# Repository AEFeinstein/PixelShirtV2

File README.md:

View this project on [CADLAB.io](https://cadlab.io/project/1073). 

# PixelShirtV2
PixelShirtV2 is an Arduino based collection of video games running on a matrix of WS2812b LEDs and controlled by [ATmega328p based wireless controllers](https://github.com/AEFeinstein/WirelessController). It's meant to be mounted on a shirt, but can be put anywhere.

## The Firmware

The firmware can be compiled two different ways. If one uses the makefile, it compiles as a Linux terminal application that uses the keyboard as input and draws to the terminal using ncurses. This is used for debugging. If one loads it into the Arduino IDE, it compiles as an Arduino executable that uses NRF24L01+ controllers as input and draws to a matrix of WS2812B LEDs.

Each game is a subclass of ArduinoGame. This allows the main function to keep an array of ArduinoGame pointers, and swap between them at runtime. The virtual functions each game must implement are:
* `void UpdatePhysics(void)` - This is called on an IRQ_HZ clock, currently 32Hz. Game state should be updated here.
* `void ProcessInput(int32_t p1, int32_t p2)` - This is called every time there is new player input, which may be more or less often than 32Hz. Each 32 bit parameter contains bitpacked analog joystick and digital button state.
* `void ResetGame(uint8_t isInit, uint8_t whoWon)` - This is called during initialization (noted by isInit). It should reset the game to a known state. It is usually called at the end of each round of a game with which player won (noted by whoWon), though that is game-specific.

The firmware uses the [Adafruit Neopixel Library](https://github.com/adafruit/Adafruit_NeoPixel) to drive the WS2812B LEDs.

The firmware uses the [nrf24L01+ Radio Library](https://github.com/kehribar/nrf24L01_plus) to talk to the controllers.

The current game roster is
* Pong - Move your paddle and don't let the ball get past you.
* Team Tetris - Like regular Tetris, but one player slides the piece while the other rotates. Each time a new piece spawns, the player roles swap.
* Lightcycle - Drive around, leaving a trail, and don't crash into either your or your opponent's trail. The field wraps around top-bottom and left-right.
* PixelFighter - A simple 2D fighter. Attack or block high or low and knock off your opponent's life bar,
* Space Invader - Two players shoot upwards as invaders slide to the left, drop, and reverse direction. The more invaders shot, the faster they go.

## The Hardware

The hardware consists of two parts, detailed below. 

### The Console

The first part is the pocket-sized console, which has the Arduino Micro, NRF24L01+ radio, two RJ45 jacks which break out Arduino pins, and two USB connectors which draw power from an external battery. There are two USB connectors because I used an external battery with two USB connectors which could each source 1A. Not that I ever turned the display on to max brightness, but 2A never hurt anyone...

Screenshots of the PCB layout, the top view is on the left and the bottom view is on the right:

This is what it looks like all soldered together:
<br>

### The Display

The second part is the chest-sized display, which has 256 WS2812B LEDs and an RJ45 connector to connect to the console for power and data. This is a one layer board, though it uses four 0-ohm resistors to jump over traces.

Screenshot of the PCB layout:
<br>

This is what it looks like all soldered together. Not pictured, RJ45 connector at the end of the cable:
<br>

## The Final Product
Here's me at Magfest 14 wearing the display mounted underneath a shirt and holding two controllers. The PixelShirtV2 is playing the PixelFighter game.
<br>

# Earlier Versions

## Version 1
The first version of the PixelShirt used blue LEDs poked through a t-shirt. The cathodes were soldered together in rows, a layer of insulating fabric was layered, then the anodes were soldered in columns. The 32 rows and columns were controlled by four daisy chained 8-bit shift registers and the display would refresh one row at a time, kind of like a CRT TV.
<br>

The upside to this design was that the LED grid was flexible and comfortable. The downside was that it wasn't mechanically strong (a few solder joints broke), the grid wasn't very regular (I'm not great with fabrics), and it just generally didn't look good. The controllers are [SparkFun Joystick Shield Kits](https://www.sparkfun.com/products/9760). 
<br>

But people seemed to get a kick out of it, so I iterated on the design. I wore it first at Magfest 12, but I think this picture is from AwesomeCon. At the time it only had Pong, Lightcycle, and Tetris.
<br>

## Version 2.0
The next year I swapped out the display for the giant PCB with RGB LEDs. Pros: colors! mechanical strength! no undershirt required! Cons: less flexible. I kept the same Sparkfun controllers. I wore this one at Magfest 13. With the advent of color, I added Space Invader.
<br>

## Version 2.1
For Magfest 14, I got over my fear of non-tethered controllers and made [wireless ones](https://github.com/AEFeinstein/WirelessController), which are mentioned above. They worked great and I didn't lose either one, but I did accidentally short their batteries a little when carelessly throwing them in a pocket. They got warm, but no harm no foul.

## Version 2.2
Magfest 15 only had software updates. I added the Fighter and Super Square games. There were no changes for Magfest 16, and I ended up not wearing it at all :(

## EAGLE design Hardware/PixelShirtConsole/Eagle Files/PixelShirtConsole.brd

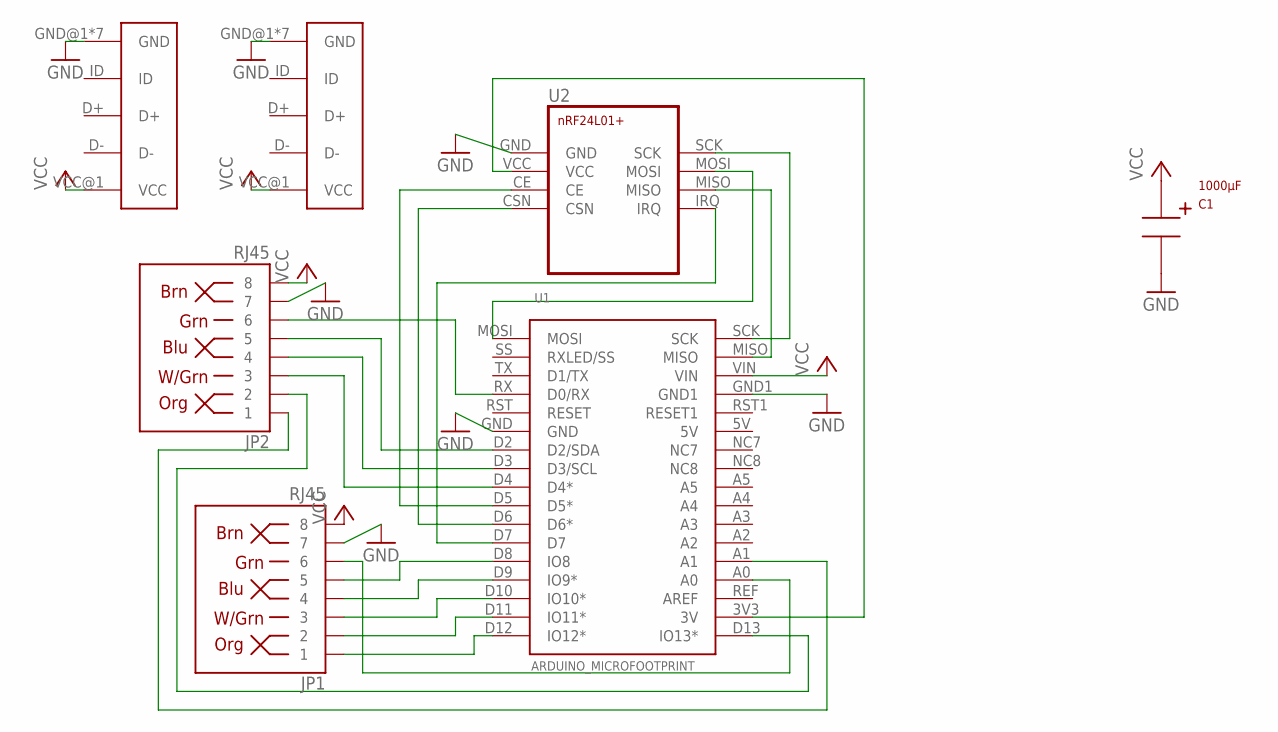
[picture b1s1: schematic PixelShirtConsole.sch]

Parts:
C1: 1000µF; CAP-CUSTOM
JP1, JP2: RJ45; RJ45-8
JP3, JP4: USB-MICRO-B
U1: ARDUINO_MICROFOOTPRINT; ARDUINO-MICRO
U2: NRF24L01+

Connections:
GND: C1.GND, JP1.7, JP2.7, JP3.GND@1 (GND), JP3.GND@2 (GND), JP3.GND@3 (GND), JP3.GND@5 (GND), JP3.GND@6 (GND), JP3.GND@7 (GND), JP3.GNF@4 (GND), JP4.GND@1 (GND), JP4.GND@2 (GND), JP4.GND@3 (GND), JP4.GND@5 (GND), JP4.GND@6 (GND), JP4.GND@7 (GND), JP4.GNF@4 (GND), U1.GND, U1.GND1, U2.GND
unnamed: U1.MISO, U2.MISO
unnamed: U1.SCK, U2.SCK
unnamed: U1.D6 (D6*), U2.CSN
unnamed: U1.D5 (D5*), U2.CE
unnamed: U1.MOSI, U2.MOSI
unnamed: U1.D7, U2.IRQ
unnamed: JP1.2, U1.D11 (IO11*)
unnamed: JP1.3, U1.D10 (IO10*)
unnamed: JP1.4, U1.D9 (IO9*)
unnamed: JP1.1, U1.D12 (IO12*)
unnamed: JP1.6, U1.A0
unnamed: JP1.5, U1.D8 (IO8)
unnamed: JP2.5, U1.D2 (D2/SDA)
unnamed: JP2.4, U1.D3 (D3/SCL)
unnamed: JP2.3, U1.D4 (D4*)
unnamed: JP2.6, U1.RX (D0/RX)
unnamed: JP2.1, U1.A1
unnamed: JP2.2, U1.D13 (IO13*)
unnamed: U1.3V3 (3V), U2.VCC
VCC: C1.VCC, JP1.8, JP2.8, JP3.VCC@1 (VCC), JP4.VCC@1 (VCC), U1.VIN

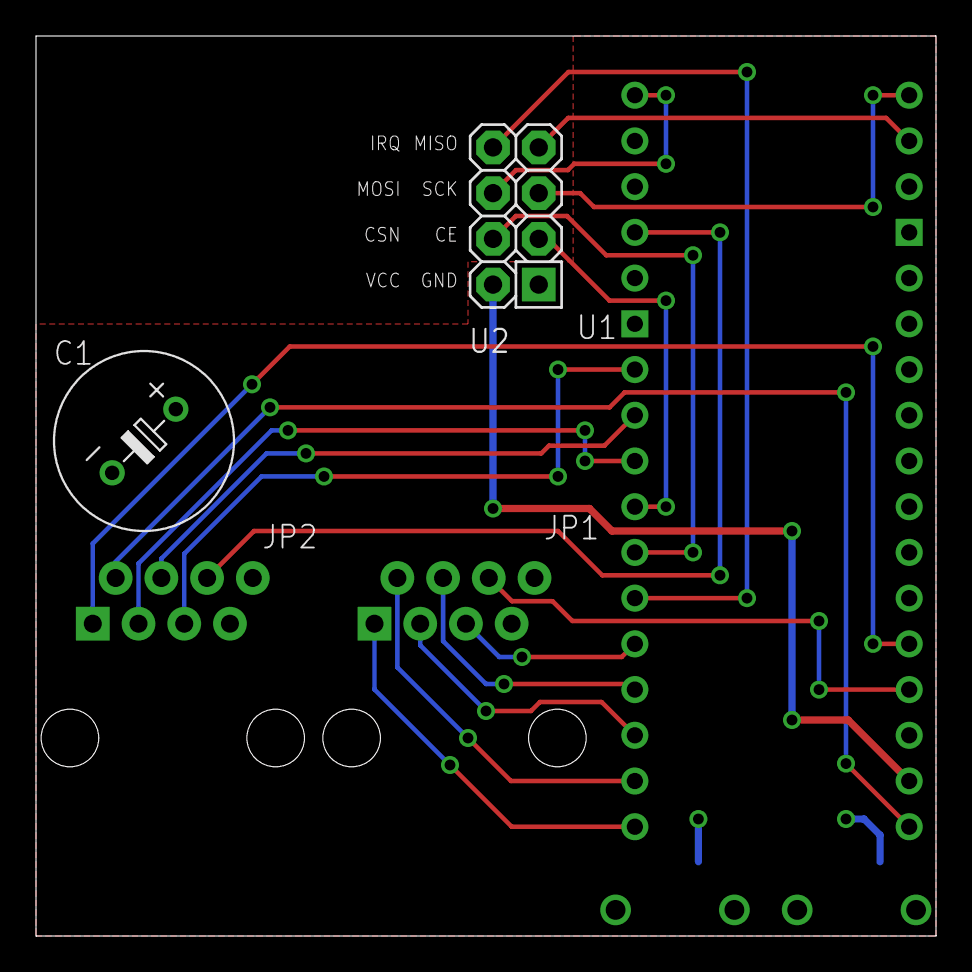
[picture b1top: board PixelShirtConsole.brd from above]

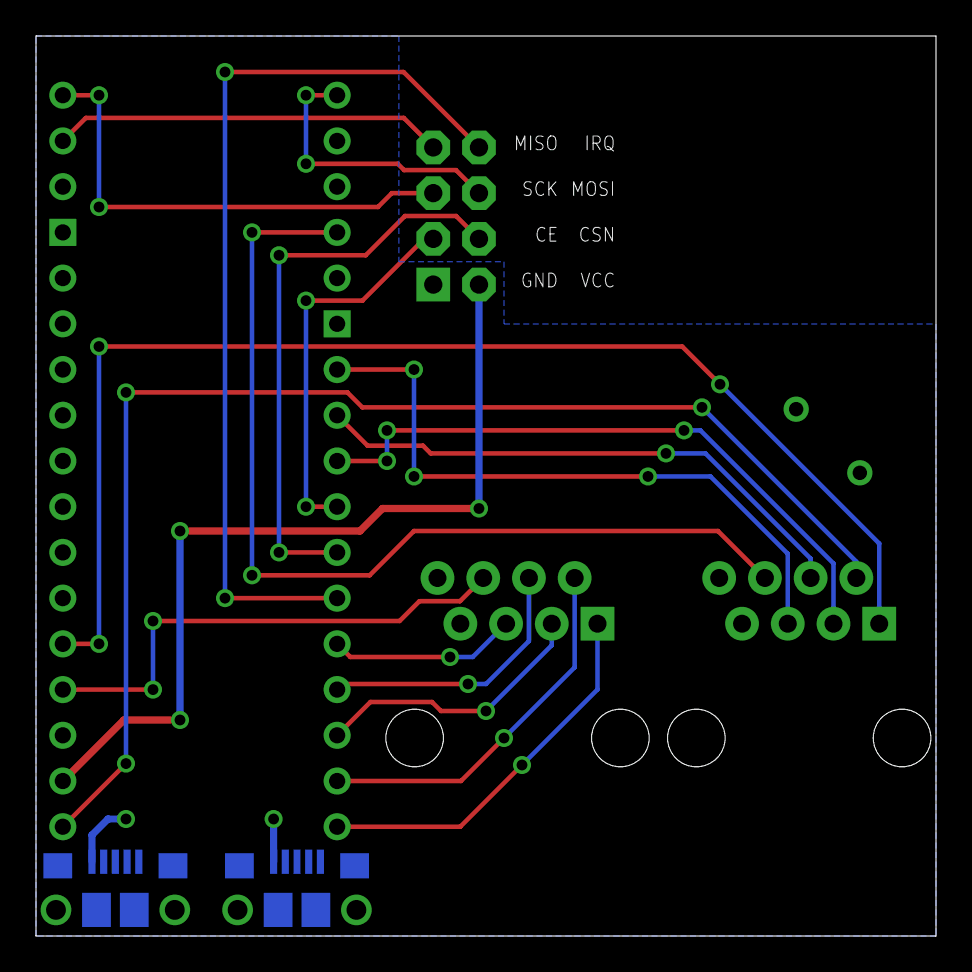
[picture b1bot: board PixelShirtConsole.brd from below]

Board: 2 copper layers, 50.0 x 50.0 mm, 7 parts (2 on the bottom side), 21 nets.

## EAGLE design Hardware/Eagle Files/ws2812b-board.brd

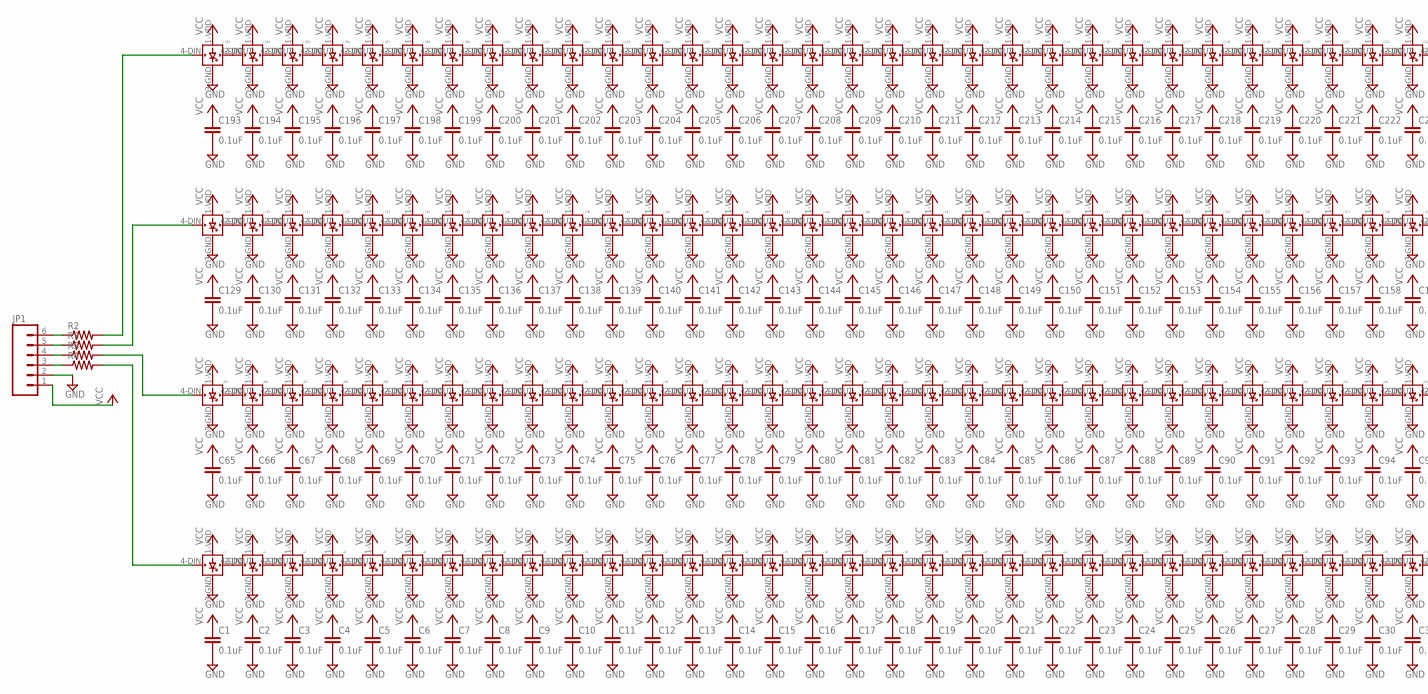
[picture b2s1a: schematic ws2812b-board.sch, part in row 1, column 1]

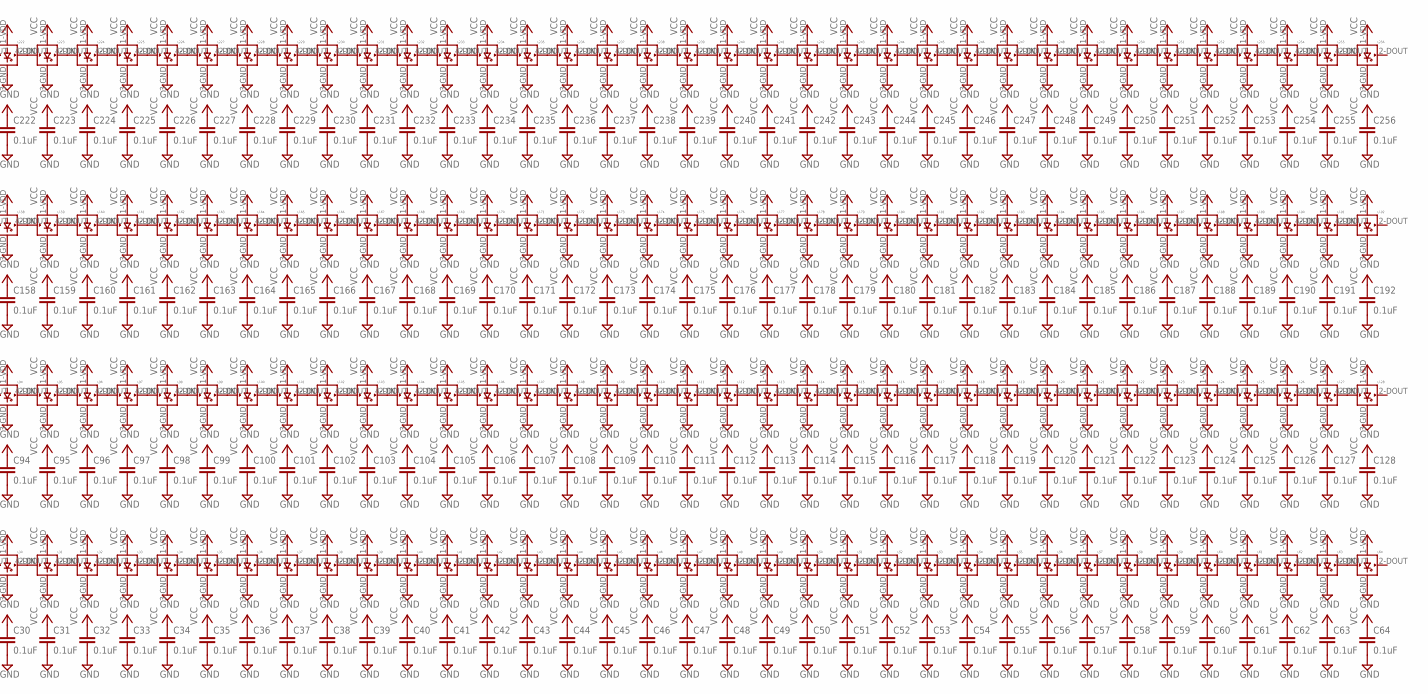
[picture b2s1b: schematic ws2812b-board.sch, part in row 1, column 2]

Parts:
C1, C2, C3, C4, C5, C6, C7, C8, C9, C10, C11, C12, C13, C14, C15, C16, C17, C18, C19, C20, C21, C22, C23, C24, C25, C26, C27, C28, C29, C30, C31, C32, C33, C34, C35, C36, C37, C38, C39, C40, C41, C42, C43, C44, C45, C46, C47, C48, C49, C50, C51, C52, C53, C54, C55, C56, C57, C58, C59, C60, C61, C62, C63, C64, C65, C66, C67, C68, C69, C70, C71, C72, C73, C74, C75, C76, C77, C78, C79, C80, C81, C82, C83, C84, C85, C86, C87, C88, C89, C90, C91, C92, C93, C94, C95, C96, C97, C98, C99, C100, C101, C102, C103, C104, C105, C106, C107, C108, C109, C110, C111, C112, C113, C114, C115, C116, C117, C118, C119, C120, C121, C122, C123, C124, C125, C126, C127, C128, C129, C130, C131, C132, C133, C134, C135, C136, C137, C138, C139, C140, C141, C142, C143, C144, C145, C146, C147, C148, C149, C150, C151, C152, C153, C154, C155, C156, C157, C158, C159, C160, C161, C162, C163, C164, C165, C166, C167, C168, C169, C170, C171, C172, C173, C174, C175, C176, C177, C178, C179, C180, C181, C182, C183, C184, C185, C186, C187, C188, C189, C190, C191, C192, C193, C194, C195, C196, C197, C198, C199, C200, C201, C202, C203, C204, C205, C206, C207, C208, C209, C210, C211, C212, C213, C214, C215, C216, C217, C218, C219, C220, C221, C222, C223, C224, C225, C226, C227, C228, C229, C230, C231, C232, C233, C234, C235, C236, C237, C238, C239, C240, C241, C242, C243, C244, C245, C246, C247, C248, C249, C250, C251, C252, C253, C254, C255, C256: 0.1uF; 0603-CAP
JP1: M06SIP; 1X06
L1, L2, L3, L4, L5, L6, L7, L8, L9, L10, L11, L12, L13, L14, L15, L16, L17, L18, L19, L20, L21, L22, L23, L24, L25, L26, L27, L28, L29, L30, L31, L32, L33, L34, L35, L36, L37, L38, L39, L40, L41, L42, L43, L44, L45, L46, L47, L48, L49, L50, L51, L52, L53, L54, L55, L56, L57, L58, L59, L60, L61, L62, L63, L64, L65, L66, L67, L68, L69, L70, L71, L72, L73, L74, L75, L76, L77, L78, L79, L80, L81, L82, L83, L84, L85, L86, L87, L88, L89, L90, L91, L92, L93, L94, L95, L96, L97, L98, L99, L100, L101, L102, L103, L104, L105, L106, L107, L108, L109, L110, L111, L112, L113, L114, L115, L116, L117, L118, L119, L120, L121, L122, L123, L124, L125, L126, L127, L128, L129, L130, L131, L132, L133, L134, L135, L136, L137, L138, L139, L140, L141, L142, L143, L144, L145, L146, L147, L148, L149, L150, L151, L152, L153, L154, L155, L156, L157, L158, L159, L160, L161, L162, L163, L164, L165, L166, L167, L168, L169, L170, L171, L172, L173, L174, L175, L176, L177, L178, L179, L180, L181, L182, L183, L184, L185, L186, L187, L188, L189, L190, L191, L192, L193, L194, L195, L196, L197, L198, L199, L200, L201, L202, L203, L204, L205, L206, L207, L208, L209, L210, L211, L212, L213, L214, L215, L216, L217, L218, L219, L220, L221, L222, L223, L224, L225, L226, L227, L228, L229, L230, L231, L232, L233, L234, L235, L236, L237, L238, L239, L240, L241, L242, L243, L244, L245, L246, L247, L248, L249, L250, L251, L252, L253, L254, L255, L256: WS2812B
R2, R3, R4, R5: RESISTOR0805-RES; 0805

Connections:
GND: C1.2, C2.2, C3.2, C4.2, C5.2, C6.2, C7.2, C8.2, C9.2, C10.2, C11.2, C12.2, C13.2, C14.2, C15.2, C16.2, C17.2, C18.2, C19.2, C20.2, C21.2, C22.2, C23.2, C24.2, C25.2, C26.2, C27.2, C28.2, C29.2, C30.2, C31.2, C32.2, C33.2, C34.2, C35.2, C36.2, C37.2, C38.2, C39.2, C40.2, C41.2, C42.2, C43.2, C44.2, C45.2, C46.2, C47.2, C48.2, C49.2, C50.2, C51.2, C52.2, C53.2, C54.2, C55.2, C56.2, C57.2, C58.2, C59.2, C60.2, C61.2, C62.2, C63.2, C64.2, C65.2, C66.2, C67.2, C68.2, C69.2, C70.2, C71.2, C72.2, C73.2, C74.2, C75.2, C76.2, C77.2, C78.2, C79.2, C80.2, C81.2, C82.2, C83.2, C84.2, C85.2, C86.2, C87.2, C88.2, C89.2, C90.2, C91.2, C92.2, C93.2, C94.2, C95.2, C96.2, C97.2, C98.2, C99.2, C100.2, C101.2, C102.2, C103.2, C104.2, C105.2, C106.2, C107.2, C108.2, C109.2, C110.2, C111.2, C112.2, C113.2, C114.2, C115.2, C116.2, C117.2, C118.2, C119.2, C120.2, C121.2, C122.2, C123.2, C124.2, C125.2, C126.2, C127.2, C128.2, C129.2, C130.2, C131.2, C132.2, C133.2, C134.2, C135.2, C136.2, C137.2, C138.2, C139.2, C140.2, C141.2, C142.2, C143.2, C144.2, C145.2, C146.2, C147.2, C148.2, C149.2, C150.2, C151.2, C152.2, C153.2, C154.2, C155.2, C156.2, C157.2, C158.2, C159.2, C160.2, C161.2, C162.2, C163.2, C164.2, C165.2, C166.2, C167.2, C168.2, C169.2, C170.2, C171.2, C172.2, C173.2, C174.2, C175.2, C176.2, C177.2, C178.2, C179.2, C180.2, C181.2, C182.2, C183.2, C184.2, C185.2, C186.2, C187.2, C188.2, C189.2, C190.2, C191.2, C192.2, C193.2, C194.2, C195.2, C196.2, C197.2, C198.2, C199.2, C200.2, C201.2, C202.2, C203.2, C204.2, C205.2, C206.2, C207.2, C208.2, C209.2, C210.2, C211.2, C212.2, C213.2, C214.2, C215.2, C216.2, C217.2, C218.2, C219.2, C220.2, C221.2, C222.2, C223.2, C224.2, C225.2, C226.2, C227.2, C228.2, C229.2, C230.2, C231.2, C232.2, C233.2, C234.2, C235.2, C236.2, C237.2, C238.2, C239.2, C240.2, C241.2, C242.2, C243.2, C244.2, C245.2, C246.2, C247.2, C248.2, C249.2, C250.2, C251.2, C252.2, C253.2, C254.2, C255.2, C256.2, JP1.2, L1.3-GND (GND), L2.3-GND (GND), L3.3-GND (GND), L4.3-GND (GND), L5.3-GND (GND), L6.3-GND (GND), L7.3-GND (GND), L8.3-GND (GND), L9.3-GND (GND), L10.3-GND (GND), L11.3-GND (GND), L12.3-GND (GND), L13.3-GND (GND), L14.3-GND (GND), L15.3-GND (GND), L16.3-GND (GND), L17.3-GND (GND), L18.3-GND (GND), L19.3-GND (GND), L20.3-GND (GND), L21.3-GND (GND), L22.3-GND (GND), L23.3-GND (GND), L24.3-GND (GND), L25.3-GND (GND), L26.3-GND (GND), L27.3-GND (GND), L28.3-GND (GND), L29.3-GND (GND), L30.3-GND (GND), L31.3-GND (GND), L32.3-GND (GND), L33.3-GND (GND), L34.3-GND (GND), L35.3-GND (GND), L36.3-GND (GND), L37.3-GND (GND), L38.3-GND (GND), L39.3-GND (GND), L40.3-GND (GND), L41.3-GND (GND), L42.3-GND (GND), L43.3-GND (GND), L44.3-GND (GND), L45.3-GND (GND), L46.3-GND (GND), L47.3-GND (GND), L48.3-GND (GND), L49.3-GND (GND), L50.3-GND (GND), L51.3-GND (GND), L52.3-GND (GND), L53.3-GND (GND), L54.3-GND (GND), L55.3-GND (GND), L56.3-GND (GND), L57.3-GND (GND), L58.3-GND (GND), L59.3-GND (GND), L60.3-GND (GND), L61.3-GND (GND), L62.3-GND (GND), L63.3-GND (GND), L64.3-GND (GND), L65.3-GND (GND), L66.3-GND (GND), L67.3-GND (GND), L68.3-GND (GND), L69.3-GND (GND), L70.3-GND (GND), L71.3-GND (GND), L72.3-GND (GND), L73.3-GND (GND), L74.3-GND (GND), L75.3-GND (GND), L76.3-GND (GND), L77.3-GND (GND), L78.3-GND (GND), L79.3-GND (GND), L80.3-GND (GND), L81.3-GND (GND), L82.3-GND (GND), L83.3-GND (GND), L84.3-GND (GND), L85.3-GND (GND), L86.3-GND (GND), L87.3-GND (GND), L88.3-GND (GND), L89.3-GND (GND), L90.3-GND (GND), L91.3-GND (GND), L92.3-GND (GND), L93.3-GND (GND), L94.3-GND (GND), L95.3-GND (GND), L96.3-GND (GND), L97.3-GND (GND), L98.3-GND (GND), L99.3-GND (GND), L100.3-GND (GND), L101.3-GND (GND), L102.3-GND (GND), L103.3-GND (GND), L104.3-GND (GND), L105.3-GND (GND), L106.3-GND (GND), L107.3-GND (GND), L108.3-GND (GND), L109.3-GND (GND), L110.3-GND (GND), L111.3-GND (GND), L112.3-GND (GND), L113.3-GND (GND), L114.3-GND (GND), L115.3-GND (GND), L116.3-GND (GND), L117.3-GND (GND), L118.3-GND (GND), L119.3-GND (GND), L120.3-GND (GND), L121.3-GND (GND), L122.3-GND (GND), L123.3-GND (GND), L124.3-GND (GND), L125.3-GND (GND), L126.3-GND (GND), L127.3-GND (GND), L128.3-GND (GND), L129.3-GND (GND), L130.3-GND (GND), L131.3-GND (GND), L132.3-GND (GND), L133.3-GND (GND), L134.3-GND (GND), L135.3-GND (GND), L136.3-GND (GND), L137.3-GND (GND), L138.3-GND (GND), L139.3-GND (GND), L140.3-GND (GND), L141.3-GND (GND), L142.3-GND (GND), L143.3-GND (GND), L144.3-GND (GND), L145.3-GND (GND), L146.3-GND (GND), L147.3-GND (GND), L148.3-GND (GND), L149.3-GND (GND), L150.3-GND (GND), L151.3-GND (GND), L152.3-GND (GND), L153.3-GND (GND)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
unnamed: L1.2-DOUT (DOUT), L2.4-DIN (DIN)
unnamed: L2.2-DOUT (DOUT), L3.4-DIN (DIN)
unnamed: L3.2-DOUT (DOUT), L4.4-DIN (DIN)
unnamed: L4.2-DOUT (DOUT), L5.4-DIN (DIN)
unnamed: L5.2-DOUT (DOUT), L6.4-DIN (DIN)
unnamed: L6.2-DOUT (DOUT), L7.4-DIN (DIN)
unnamed: L7.2-DOUT (DOUT), L8.4-DIN (DIN)
unnamed: L8.2-DOUT (DOUT), L9.4-DIN (DIN)
unnamed: L9.2-DOUT (DOUT), L10.4-DIN (DIN)
unnamed: L10.2-DOUT (DOUT), L11.4-DIN (DIN)
unnamed: L11.2-DOUT (DOUT), L12.4-DIN (DIN)
unnamed: L12.2-DOUT (DOUT), L13.4-DIN (DIN)
unnamed: L13.2-DOUT (DOUT), L14.4-DIN (DIN)
unnamed: L14.2-DOUT (DOUT), L15.4-DIN (DIN)
unnamed: L15.2-DOUT (DOUT), L16.4-DIN (DIN)
unnamed: L16.2-DOUT (DOUT), L17.4-DIN (DIN)
unnamed: L17.2-DOUT (DOUT), L18.4-DIN (DIN)
unnamed: L18.2-DOUT (DOUT), L19.4-DIN (DIN)
unnamed: L19.2-DOUT (DOUT), L20.4-DIN (DIN)
unnamed: L20.2-DOUT (DOUT), L21.4-DIN (DIN)
unnamed: L21.2-DOUT (DOUT), L22.4-DIN (DIN)
unnamed: L22.2-DOUT (DOUT), L23.4-DIN (DIN)
unnamed: L23.2-DOUT (DOUT), L24.4-DIN (DIN)
unnamed: L24.2-DOUT (DOUT), L25.4-DIN (DIN)
unnamed: L25.2-DOUT (DOUT), L26.4-DIN (DIN)
unnamed: L26.2-DOUT (DOUT), L27.4-DIN (DIN)
unnamed: L27.2-DOUT (DOUT), L28.4-DIN (DIN)
unnamed: L28.2-DOUT (DOUT), L29.4-DIN (DIN)
unnamed: L29.2-DOUT (DOUT), L30.4-DIN (DIN)
unnamed: L30.2-DOUT (DOUT), L31.4-DIN (DIN)
unnamed: L31.2-DOUT (DOUT), L32.4-DIN (DIN)
unnamed: L32.2-DOUT (DOUT), L33.4-DIN (DIN)
unnamed: L33.2-DOUT (DOUT), L34.4-DIN (DIN)
unnamed: L34.2-DOUT (DOUT), L35.4-DIN (DIN)
unnamed: L35.2-DOUT (DOUT), L36.4-DIN (DIN)
unnamed: L36.2-DOUT (DOUT), L37.4-DIN (DIN)
unnamed: L37.2-DOUT (DOUT), L38.4-DIN (DIN)
unnamed: L38.2-DOUT (DOUT), L39.4-DIN (DIN)
unnamed: L39.2-DOUT (DOUT), L40.4-DIN (DIN)
unnamed: L40.2-DOUT (DOUT), L41.4-DIN (DIN)
unnamed: L41.2-DOUT (DOUT), L42.4-DIN (DIN)
unnamed: L42.2-DOUT (DOUT), L43.4-DIN (DIN)
unnamed: L43.2-DOUT (DOUT), L44.4-DIN (DIN)
unnamed: L44.2-DOUT (DOUT), L45.4-DIN (DIN)
unnamed: L45.2-DOUT (DOUT), L46.4-DIN (DIN)
unnamed: L46.2-DOUT (DOUT), L47.4-DIN (DIN)
unnamed: L47.2-DOUT (DOUT), L48.4-DIN (DIN)
unnamed: L48.2-DOUT (DOUT), L49.4-DIN (DIN)
unnamed: L49.2-DOUT (DOUT), L50.4-DIN (DIN)
unnamed: L50.2-DOUT (DOUT), L51.4-DIN (DIN)
unnamed: L51.2-DOUT (DOUT), L52.4-DIN (DIN)
unnamed: L52.2-DOUT (DOUT), L53.4-DIN (DIN)
unnamed: L53.2-DOUT (DOUT), L54.4-DIN (DIN)
unnamed: L54.2-DOUT (DOUT), L55.4-DIN (DIN)
unnamed: L55.2-DOUT (DOUT), L56.4-DIN (DIN)
unnamed: L56.2-DOUT (DOUT), L57.4-DIN (DIN)
unnamed: L57.2-DOUT (DOUT), L58.4-DIN (DIN)
unnamed: L58.2-DOUT (DOUT), L59.4-DIN (DIN)
unnamed: L59.2-DOUT (DOUT), L60.4-DIN (DIN)
unnamed: L60.2-DOUT (DOUT), L61.4-DIN (DIN)
unnamed: L61.2-DOUT (DOUT), L62.4-DIN (DIN)
unnamed: L62.2-DOUT (DOUT), L63.4-DIN (DIN)
unnamed: L63.2-DOUT (DOUT), L64.4-DIN (DIN)
unnamed: L65.2-DOUT (DOUT), L66.4-DIN (DIN)
unnamed: L66.2-DOUT (DOUT), L67.4-DIN (DIN)
unnamed: L67.2-DOUT (DOUT), L68.4-DIN (DIN)
unnamed: L68.2-DOUT (DOUT), L69.4-DIN (DIN)
unnamed: L69.2-DOUT (DOUT), L70.4-DIN (DIN)
unnamed: L70.2-DOUT (DOUT), L71.4-DIN (DIN)
unnamed: L71.2-DOUT (DOUT), L72.4-DIN (DIN)
unnamed: L72.2-DOUT (DOUT), L73.4-DIN (DIN)
unnamed: L73.2-DOUT (DOUT), L74.4-DIN (DIN)
unnamed: L74.2-DOUT (DOUT), L75.4-DIN (DIN)
unnamed: L75.2-DOUT (DOUT), L76.4-DIN (DIN)
unnamed: L76.2-DOUT (DOUT), L77.4-DIN (DIN)
unnamed: L77.2-DOUT (DOUT), L78.4-DIN (DIN)
unnamed: L78.2-DOUT (DOUT), L79.4-DIN (DIN)
unnamed: L79.2-DOUT (DOUT), L80.4-DIN (DIN)
unnamed: L80.2-DOUT (DOUT), L81.4-DIN (DIN)
unnamed: L81.2-DOUT (DOUT), L82.4-DIN (DIN)
unnamed: L82.2-DOUT (DOUT), L83.4-DIN (DIN)
unnamed: L83.2-DOUT (DOUT), L84.4-DIN (DIN)
unnamed: L84.2-DOUT (DOUT), L85.4-DIN (DIN)
unnamed: L85.2-DOUT (DOUT), L86.4-DIN (DIN)
unnamed: L86.2-DOUT (DOUT), L87.4-DIN (DIN)
unnamed: L87.2-DOUT (DOUT), L88.4-DIN (DIN)
unnamed: L88.2-DOUT (DOUT), L89.4-DIN (DIN)
unnamed: L89.2-DOUT (DOUT), L90.4-DIN (DIN)
unnamed: L90.2-DOUT (DOUT), L91.4-DIN (DIN)
unnamed: L91.2-DOUT (DOUT), L92.4-DIN (DIN)
unnamed: L92.2-DOUT (DOUT), L93.4-DIN (DIN)
unnamed: L93.2-DOUT (DOUT), L94.4-DIN (DIN)
unnamed: L94.2-DOUT (DOUT), L95.4-DIN (DIN)
unnamed: L95.2-DOUT (DOUT), L96.4-DIN (DIN)
unnamed: L96.2-DOUT (DOUT), L97.4-DIN (DIN)
unnamed: L97.2-DOUT (DOUT), L98.4-DIN (DIN)
unnamed: L98.2-DOUT (DOUT), L99.4-DIN (DIN)
unnamed: L99.2-DOUT (DOUT), L100.4-DIN (DIN)
unnamed: L100.2-DOUT (DOUT), L101.4-DIN (DIN)
unnamed: L101.2-DOUT (DOUT), L102.4-DIN (DIN)
unnamed: L102.2-DOUT (DOUT), L103.4-DIN (DIN)
unnamed: L103.2-DOUT (DOUT), L104.4-DIN (DIN)
unnamed: L104.2-DOUT (DOUT), L105.4-DIN (DIN)
unnamed: L105.2-DOUT (DOUT), L106.4-DIN (DIN)
unnamed: L106.2-DOUT (DOUT), L107.4-DIN (DIN)
unnamed: L107.2-DOUT (DOUT), L108.4-DIN (DIN)
unnamed: L108.2-DOUT (DOUT), L109.4-DIN (DIN)
unnamed: L109.2-DOUT (DOUT), L110.4-DIN (DIN)
unnamed: L110.2-DOUT (DOUT), L111.4-DIN (DIN)
unnamed: L111.2-DOUT (DOUT), L112.4-DIN (DIN)
unnamed: L112.2-DOUT (DOUT), L113.4-DIN (DIN)
unnamed: L113.2-DOUT (DOUT), L114.4-DIN (DIN)
unnamed: L114.2-DOUT (DOUT), L115.4-DIN (DIN)
unnamed: L115.2-DOUT (DOUT), L116.4-DIN (DIN)
unnamed: L116.2-DOUT (DOUT), L117.4-DIN (DIN)
unnamed: L117.2-DOUT (DOUT), L118.4-DIN (DIN)
unnamed: L118.2-DOUT (DOUT), L119.4-DIN (DIN)
unnamed: L119.2-DOUT (DOUT), L120.4-DIN (DIN)
unnamed: L120.2-DOUT (DOUT), L121.4-DIN (DIN)
unnamed: L121.2-DOUT (DOUT), L122.4-DIN (DIN)
unnamed: L122.2-DOUT (DOUT), L123.4-DIN (DIN)
unnamed: L123.2-DOUT (DOUT), L124.4-DIN (DIN)
unnamed: L124.2-DOUT (DOUT), L125.4-DIN (DIN)
unnamed: L125.2-DOUT (DOUT), L126.4-DIN (DIN)
unnamed: L126.2-DOUT (DOUT), L127.4-DIN (DIN)
unnamed: L127.2-DOUT (DOUT), L128.4-DIN (DIN)
unnamed: L129.2-DOUT (DOUT), L130.4-DIN (DIN)
unnamed: L130.2-DOUT (DOUT), L131.4-DIN (DIN)
unnamed: L131.2-DOUT (DOUT), L132.4-DIN (DIN)
unnamed: L132.2-DOUT (DOUT), L133.4-DIN (DIN)
unnamed: L133.2-DOUT (DOUT), L134.4-DIN (DIN)
unnamed: L134.2-DOUT (DOUT), L135.4-DIN (DIN)
unnamed: L135.2-DOUT (DOUT), L136.4-DIN (DIN)
unnamed: L136.2-DOUT (DOUT), L137.4-DIN (DIN)
unnamed: L137.2-DOUT (DOUT), L138.4-DIN (DIN)
unnamed: L138.2-DOUT (DOUT), L139.4-DIN (DIN)
unnamed: L139.2-DOUT (DOUT), L140.4-DIN (DIN)
unnamed: L140.2-DOUT (DOUT), L141.4-DIN (DIN)
unnamed: L141.2-DOUT (DOUT), L142.4-DIN (DIN)
unnamed: L142.2-DOUT (DOUT), L143.4-DIN (DIN)
unnamed: L143.2-DOUT (DOUT), L144.4-DIN (DIN)
unnamed: L144.2-DOUT (DOUT), L145.4-DIN (DIN)
unnamed: L145.2-DOUT (DOUT), L146.4-DIN (DIN)
unnamed: L146.2-DOUT (DOUT), L147.4-DIN (DIN)
unnamed: L147.2-DOUT (DOUT), L148.4-DIN (DIN)
unnamed: L148.2-DOUT (DOUT), L149.4-DIN (DIN)
unnamed: L149.2-DOUT (DOUT), L150.4-DIN (DIN)
unnamed: L150.2-DOUT (DOUT), L151.4-DIN (DIN)
unnamed: L151.2-DOUT (DOUT), L152.4-DIN (DIN)
unnamed: L152.2-DOUT (DOUT), L153.4-DIN (DIN)
unnamed: L153.2-DOUT (DOUT), L154.4-DIN (DIN)
unnamed: L154.2-DOUT (DOUT), L155.4-DIN (DIN)
unnamed: L155.2-DOUT (DOUT), L156.4-DIN (DIN)
unnamed: L156.2-DOUT (DOUT), L157.4-DIN (DIN)
unnamed: L157.2-DOUT (DOUT), L158.4-DIN (DIN)
unnamed: L158.2-DOUT (DOUT), L159.4-DIN (DIN)
unnamed: L159.2-DOUT (DOUT), L160.4-DIN (DIN)
unnamed: L160.2-DOUT (DOUT), L161.4-DIN (DIN)
unnamed: L161.2-DOUT (DOUT), L162.4-DIN (DIN)
unnamed: L162.2-DOUT (DOUT), L163.4-DIN (DIN)
unnamed: L163.2-DOUT (DOUT), L164.4-DIN (DIN)
unnamed: L164.2-DOUT (DOUT), L165.4-DIN (DIN)
unnamed: L165.2-DOUT (DOUT), L166.4-DIN (DIN)
unnamed: L166.2-DOUT (DOUT), L167.4-DIN (DIN)
unnamed: L167.2-DOUT (DOUT), L168.4-DIN (DIN)
unnamed: L168.2-DOUT (DOUT), L169.4-DIN (DIN)
unnamed: L169.2-DOUT (DOUT), L170.4-DIN (DIN)
unnamed: L170.2-DOUT (DOUT), L171.4-DIN (DIN)
unnamed: L171.2-DOUT (DOUT), L172.4-DIN (DIN)
unnamed: L172.2-DOUT (DOUT), L173.4-DIN (DIN)
unnamed: L173.2-DOUT (DOUT), L174.4-DIN (DIN)
unnamed: L174.2-DOUT (DOUT), L175.4-DIN (DIN)
unnamed: L175.2-DOUT (DOUT), L176.4-DIN (DIN)
unnamed: L176.2-DOUT (DOUT), L177.4-DIN (DIN)
unnamed: L177.2-DOUT (DOUT), L178.4-DIN (DIN)
unnamed: L178.2-DOUT (DOUT), L179.4-DIN (DIN)
unnamed: L179.2-DOUT (DOUT), L180.4-DIN (DIN)
unnamed: L180.2-DOUT (DOUT), L181.4-DIN (DIN)
unnamed: L181.2-DOUT (DOUT), L182.4-DIN (DIN)
unnamed: L182.2-DOUT (DOUT), L183.4-DIN (DIN)
unnamed: L183.2-DOUT (DOUT), L184.4-DIN (DIN)
unnamed: L184.2-DOUT (DOUT), L185.4-DIN (DIN)
unnamed: L185.2-DOUT (DOUT), L186.4-DIN (DIN)
unnamed: L186.2-DOUT (DOUT), L187.4-DIN (DIN)
unnamed: L187.2-DOUT (DOUT), L188.4-DIN (DIN)
unnamed: L188.2-DOUT (DOUT), L189.4-DIN (DIN)
unnamed: L189.2-DOUT (DOUT), L190.4-DIN (DIN)
unnamed: L190.2-DOUT (DOUT), L191.4-DIN (DIN)
unnamed: L191.2-DOUT (DOUT), L192.4-DIN (DIN)
unnamed: L193.2-DOUT (DOUT), L194.4-DIN (DIN)
unnamed: L194.2-DOUT (DOUT), L195.4-DIN (DIN)
unnamed: L195.2-DOUT (DOUT), L196.4-DIN (DIN)
unnamed: L196.2-DOUT (DOUT), L197.4-DIN (DIN)
unnamed: L197.2-DOUT (DOUT), L198.4-DIN (DIN)
unnamed: L198.2-DOUT (DOUT), L199.4-DIN (DIN)
unnamed: L199.2-DOUT (DOUT), L200.4-DIN (DIN)
unnamed: L200.2-DOUT (DOUT), L201.4-DIN (DIN)
unnamed: L201.2-DOUT (DOUT), L202.4-DIN (DIN)
unnamed: L202.2-DOUT (DOUT), L203.4-DIN (DIN)
unnamed: L203.2-DOUT (DOUT), L204.4-DIN (DIN)
unnamed: L204.2-DOUT (DOUT), L205.4-DIN (DIN)
unnamed: L205.2-DOUT (DOUT), L206.4-DIN (DIN)
unnamed: L206.2-DOUT (DOUT), L207.4-DIN (DIN)
unnamed: L207.2-DOUT (DOUT), L208.4-DIN (DIN)
unnamed: L208.2-DOUT (DOUT), L209.4-DIN (DIN)
unnamed: L209.2-DOUT (DOUT), L210.4-DIN (DIN)
unnamed: L210.2-DOUT (DOUT), L211.4-DIN (DIN)
unnamed: L211.2-DOUT (DOUT), L212.4-DIN (DIN)
unnamed: L212.2-DOUT (DOUT), L213.4-DIN (DIN)
unnamed: L213.2-DOUT (DOUT), L214.4-DIN (DIN)
unnamed: L214.2-DOUT (DOUT), L215.4-DIN (DIN)
unnamed: L215.2-DOUT (DOUT), L216.4-DIN (DIN)
unnamed: L216.2-DOUT (DOUT), L217.4-DIN (DIN)
unnamed: L217.2-DOUT (DOUT), L218.4-DIN (DIN)
unnamed: L218.2-DOUT (DOUT), L219.4-DIN (DIN)
unnamed: L219.2-DOUT (DOUT), L220.4-DIN (DIN)
unnamed: L220.2-DOUT (DOUT), L221.4-DIN (DIN)
unnamed: L221.2-DOUT (DOUT), L222.4-DIN (DIN)
unnamed: L222.2-DOUT (DOUT), L223.4-DIN (DIN)
unnamed: L223.2-DOUT (DOUT), L224.4-DIN (DIN)
unnamed: L224.2-DOUT (DOUT), L225.4-DIN (DIN)
unnamed: L225.2-DOUT (DOUT), L226.4-DIN (DIN)
unnamed: L226.2-DOUT (DOUT), L227.4-DIN (DIN)
unnamed: L227.2-DOUT (DOUT), L228.4-DIN (DIN)
unnamed: L228.2-DOUT (DOUT), L229.4-DIN (DIN)
unnamed: L229.2-DOUT (DOUT), L230.4-DIN (DIN)
unnamed: L230.2-DOUT (DOUT), L231.4-DIN (DIN)
unnamed: L231.2-DOUT (DOUT), L232.4-DIN (DIN)
unnamed: L232.2-DOUT (DOUT), L233.4-DIN (DIN)
unnamed: L233.2-DOUT (DOUT), L234.4-DIN (DIN)
unnamed: L234.2-DOUT (DOUT), L235.4-DIN (DIN)
unnamed: L235.2-DOUT (DOUT), L236.4-DIN (DIN)
unnamed: L236.2-DOUT (DOUT), L237.4-DIN (DIN)
unnamed: L237.2-DOUT (DOUT), L238.4-DIN (DIN)
unnamed: L238.2-DOUT (DOUT), L239.4-DIN (DIN)
unnamed: L239.2-DOUT (DOUT), L240.4-DIN (DIN)
unnamed: L240.2-DOUT (DOUT), L241.4-DIN (DIN)
unnamed: L241.2-DOUT (DOUT), L242.4-DIN (DIN)
unnamed: L242.2-DOUT (DOUT), L243.4-DIN (DIN)
unnamed: L243.2-DOUT (DOUT), L244.4-DIN (DIN)
unnamed: L244.2-DOUT (DOUT), L245.4-DIN (DIN)
unnamed: L245.2-DOUT (DOUT), L246.4-DIN (DIN)
unnamed: L246.2-DOUT (DOUT), L247.4-DIN (DIN)
unnamed: L247.2-DOUT (DOUT), L248.4-DIN (DIN)
unnamed: L248.2-DOUT (DOUT), L249.4-DIN (DIN)
unnamed: L249.2-DOUT (DOUT), L250.4-DIN (DIN)
unnamed: L250.2-DOUT (DOUT), L251.4-DIN (DIN)
unnamed: L251.2-DOUT (DOUT), L252.4-DIN (DIN)
unnamed: L252.2-DOUT (DOUT), L253.4-DIN (DIN)
unnamed: L253.2-DOUT (DOUT), L254.4-DIN (DIN)
unnamed: L254.2-DOUT (DOUT), L255.4-DIN (DIN)
unnamed: L255.2-DOUT (DOUT), L256.4-DIN (DIN)
unnamed: L1.4-DIN (DIN), R4.2
unnamed: L65.4-DIN (DIN), R5.2
unnamed: L193.4-DIN (DIN), R2.2
unnamed: L129.4-DIN (DIN), R3.2
unnamed: JP1.6, R2.1
unnamed: JP1.5, R3.1
unnamed: JP1.4, R5.1
unnamed: JP1.3, R4.1
VCC: C1.1, C2.1, C3.1, C4.1, C5.1, C6.1, C7.1, C8.1, C9.1, C10.1, C11.1, C12.1, C13.1, C14.1, C15.1, C16.1, C17.1, C18.1, C19.1, C20.1, C21.1, C22.1, C23.1, C24.1, C25.1, C26.1, C27.1, C28.1, C29.1, C30.1, C31.1, C32.1, C33.1, C34.1, C35.1, C36.1, C37.1, C38.1, C39.1, C40.1, C41.1, C42.1, C43.1, C44.1, C45.1, C46.1, C47.1, C48.1, C49.1, C50.1, C51.1, C52.1, C53.1, C54.1, C55.1, C56.1, C57.1, C58.1, C59.1, C60.1, C61.1, C62.1, C63.1, C64.1, C65.1, C66.1, C67.1, C68.1, C69.1, C70.1, C71.1, C72.1, C73.1, C74.1, C75.1, C76.1, C77.1, C78.1, C79.1, C80.1, C81.1, C82.1, C83.1, C84.1, C85.1, C86.1, C87.1, C88.1, C89.1, C90.1, C91.1, C92.1, C93.1, C94.1, C95.1, C96.1, C97.1, C98.1, C99.1, C100.1, C101.1, C102.1, C103.1, C104.1, C105.1, C106.1, C107.1, C108.1, C109.1, C110.1, C111.1, C112.1, C113.1, C114.1, C115.1, C116.1, C117.1, C118.1, C119.1, C120.1, C121.1, C122.1, C123.1, C124.1, C125.1, C126.1, C127.1, C128.1, C129.1, C130.1, C131.1, C132.1, C133.1, C134.1, C135.1, C136.1, C137.1, C138.1, C139.1, C140.1, C141.1, C142.1, C143.1, C144.1, C145.1, C146.1, C147.1, C148.1, C149.1, C150.1, C151.1, C152.1, C153.1, C154.1, C155.1, C156.1, C157.1, C158.1, C159.1, C160.1, C161.1, C162.1, C163.1, C164.1, C165.1, C166.1, C167.1, C168.1, C169.1, C170.1, C171.1, C172.1, C173.1, C174.1, C175.1, C176.1, C177.1, C178.1, C179.1, C180.1, C181.1, C182.1, C183.1, C184.1, C185.1, C186.1, C187.1, C188.1, C189.1, C190.1, C191.1, C192.1, C193.1, C194.1, C195.1, C196.1, C197.1, C198.1, C199.1, C200.1, C201.1, C202.1, C203.1, C204.1, C205.1, C206.1, C207.1, C208.1, C209.1, C210.1, C211.1, C212.1, C213.1, C214.1, C215.1, C216.1, C217.1, C218.1, C219.1, C220.1, C221.1, C222.1, C223.1, C224.1, C225.1, C226.1, C227.1, C228.1, C229.1, C230.1, C231.1, C232.1, C233.1, C234.1, C235.1, C236.1, C237.1, C238.1, C239.1, C240.1, C241.1, C242.1, C243.1, C244.1, C245.1, C246.1, C247.1, C248.1, C249.1, C250.1, C251.1, C252.1, C253.1, C254.1, C255.1, C256.1, JP1.1, L1.1-VDD (VDD), L2.1-VDD (VDD), L3.1-VDD (VDD), L4.1-VDD (VDD), L5.1-VDD (VDD), L6.1-VDD (VDD), L7.1-VDD (VDD), L8.1-VDD (VDD), L9.1-VDD (VDD), L10.1-VDD (VDD), L11.1-VDD (VDD), L12.1-VDD (VDD), L13.1-VDD (VDD), L14.1-VDD (VDD), L15.1-VDD (VDD), L16.1-VDD (VDD), L17.1-VDD (VDD), L18.1-VDD (VDD), L19.1-VDD (VDD), L20.1-VDD (VDD), L21.1-VDD (VDD), L22.1-VDD (VDD), L23.1-VDD (VDD), L24.1-VDD (VDD), L25.1-VDD (VDD), L26.1-VDD (VDD), L27.1-VDD (VDD), L28.1-VDD (VDD), L29.1-VDD (VDD), L30.1-VDD (VDD), L31.1-VDD (VDD), L32.1-VDD (VDD), L33.1-VDD (VDD), L34.1-VDD (VDD), L35.1-VDD (VDD), L36.1-VDD (VDD), L37.1-VDD (VDD), L38.1-VDD (VDD), L39.1-VDD (VDD), L40.1-VDD (VDD), L41.1-VDD (VDD), L42.1-VDD (VDD), L43.1-VDD (VDD), L44.1-VDD (VDD), L45.1-VDD (VDD), L46.1-VDD (VDD), L47.1-VDD (VDD), L48.1-VDD (VDD), L49.1-VDD (VDD), L50.1-VDD (VDD), L51.1-VDD (VDD), L52.1-VDD (VDD), L53.1-VDD (VDD), L54.1-VDD (VDD), L55.1-VDD (VDD), L56.1-VDD (VDD), L57.1-VDD (VDD), L58.1-VDD (VDD), L59.1-VDD (VDD), L60.1-VDD (VDD), L61.1-VDD (VDD), L62.1-VDD (VDD), L63.1-VDD (VDD), L64.1-VDD (VDD), L65.1-VDD (VDD), L66.1-VDD (VDD), L67.1-VDD (VDD), L68.1-VDD (VDD), L69.1-VDD (VDD), L70.1-VDD (VDD), L71.1-VDD (VDD), L72.1-VDD (VDD), L73.1-VDD (VDD), L74.1-VDD (VDD), L75.1-VDD (VDD), L76.1-VDD (VDD), L77.1-VDD (VDD), L78.1-VDD (VDD), L79.1-VDD (VDD), L80.1-VDD (VDD), L81.1-VDD (VDD), L82.1-VDD (VDD), L83.1-VDD (VDD), L84.1-VDD (VDD), L85.1-VDD (VDD), L86.1-VDD (VDD), L87.1-VDD (VDD), L88.1-VDD (VDD), L89.1-VDD (VDD), L90.1-VDD (VDD), L91.1-VDD (VDD), L92.1-VDD (VDD), L93.1-VDD (VDD), L94.1-VDD (VDD), L95.1-VDD (VDD), L96.1-VDD (VDD), L97.1-VDD (VDD), L98.1-VDD (VDD), L99.1-VDD (VDD), L100.1-VDD (VDD), L101.1-VDD (VDD), L102.1-VDD (VDD), L103.1-VDD (VDD), L104.1-VDD (VDD), L105.1-VDD (VDD), L106.1-VDD (VDD), L107.1-VDD (VDD), L108.1-VDD (VDD), L109.1-VDD (VDD), L110.1-VDD (VDD), L111.1-VDD (VDD), L112.1-VDD (VDD), L113.1-VDD (VDD), L114.1-VDD (VDD), L115.1-VDD (VDD), L116.1-VDD (VDD), L117.1-VDD (VDD), L118.1-VDD (VDD), L119.1-VDD (VDD), L120.1-VDD (VDD), L121.1-VDD (VDD), L122.1-VDD (VDD), L123.1-VDD (VDD), L124.1-VDD (VDD), L125.1-VDD (VDD), L126.1-VDD (VDD), L127.1-VDD (VDD), L128.1-VDD (VDD), L129.1-VDD (VDD), L130.1-VDD (VDD), L131.1-VDD (VDD), L132.1-VDD (VDD), L133.1-VDD (VDD), L134.1-VDD (VDD), L135.1-VDD (VDD), L136.1-VDD (VDD), L137.1-VDD (VDD), L138.1-VDD (VDD), L139.1-VDD (VDD), L140.1-VDD (VDD), L141.1-VDD (VDD), L142.1-VDD (VDD), L143.1-VDD (VDD), L144.1-VDD (VDD), L145.1-VDD (VDD), L146.1-VDD (VDD), L147.1-VDD (VDD), L148.1-VDD (VDD), L149.1-VDD (VDD), L150.1-VDD (VDD), L151.1-VDD (VDD), L152.1-VDD (VDD), L153.1-VDD (VDD)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

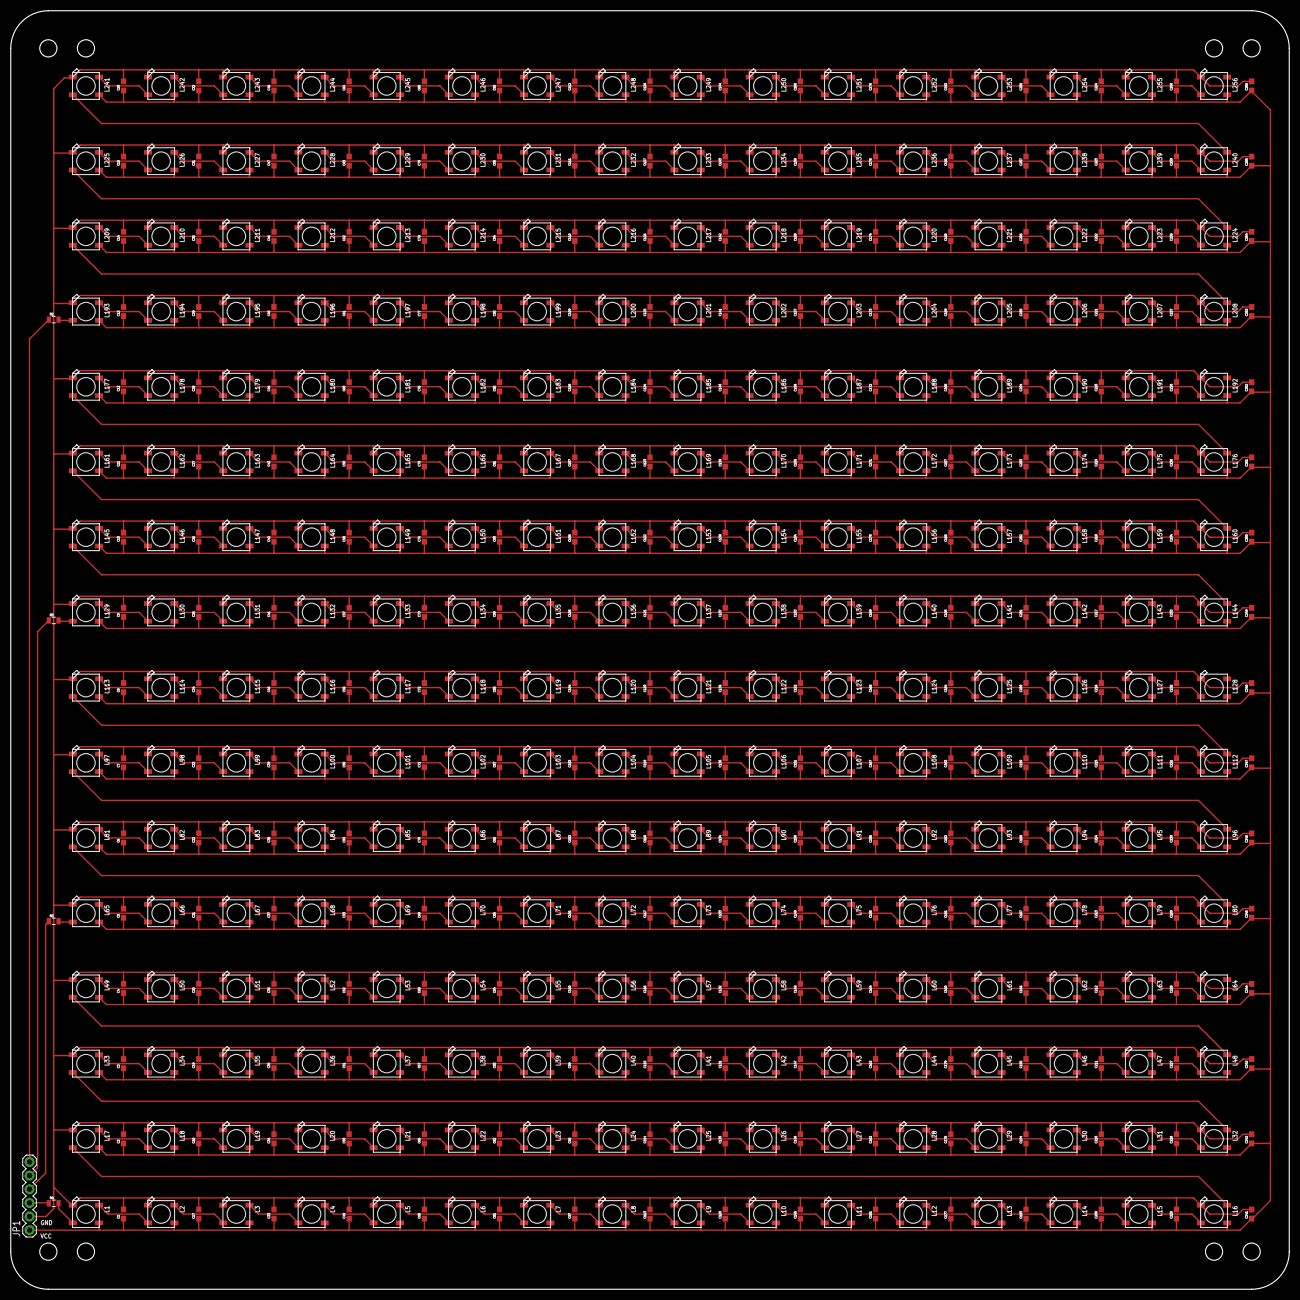
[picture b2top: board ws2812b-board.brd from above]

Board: 2 copper layers, 238.0 x 238.0 mm, 517 parts (0 on the bottom side), 262 nets.

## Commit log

2015-01-21 Added initial Arduino projects and Eagle & Gerber files for the LED matrix board.
2015-01-21 Formatting
2015-01-21 Better collision detection
2015-01-21 Added screensaver. totally untested, but it compiles
2015-01-21 Slowed down the screensaver
2015-01-22 Screensaver is now actually drawn Turned really thick line into a square wave Fixed square wave size Fixed screensaver timeout button checks Fixed screen clear & game reset when leaving the screensav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
2015-01-22 Fixed screensaver timeout
2015-01-26 Fixed issue where green was OP
2015-05-05 Removed double frame buffer (my 2D array & internal NeoPixel structure) Removed I2C code for GPU communication Added NeoPixel driver code Removed GPIO polling for controllers Added nRF wireless contr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
2015-05-09 Changed Pixel & nRF pins for prototyping Removed screen transposition Sped up heartbeat Initialized controller state & fixed button reading
2015-05-09 Removed PixelGPU code, no longer necessary
2015-05-09 Moved LED_Board files into it's own folder
2015-05-09 Changed name from LED_Board to PixelShirtDisplay
2015-05-09 Added PixelShirtConsole EAGLE files
2015-05-10 Moved some parts around for clearance Added logo, name Added Gerber files
2015-05-12 Remade gerber files with EAGLE 6.6. Added dimension layer in .pls and .plc
2015-05-13 Fixed SuperSquare for new pixel scheme, new direction bitmask
2015-05-13 Fixed color checks for Shooter
2015-05-13 Changed all colors to use uint32_t, rather than three uint8_ts #defined a bunch of colors Consistent P1 & P2 colors across all games
2015-05-13 Fixed Y axis for new controller
2015-05-13 Fixed warnings for uninitialized variables
2015-05-13 astylin'
2015-05-16 Added support for multiple controllers
2015-05-23 Modified pin definitions for new board Fixed schematic issue where the nRF had 5V powering it instead of 3.3V
2015-05-24 Fixed screensaver not shifting properly
2015-05-30 Unrandomized tetromino colors with evenly spaced values around the color wheel
2015-06-01 Sped up screensaver, fixed colors Picked better tetris colors
2015-07-30 Refactored input processing to take two arguments instead of ten
    Started adding stubs for doxygen comments
2015-07-30 Changed comment style
2015-07-30 Empty doxygen comments
2015-09-05 Added explicit void instead of empty parenthesis.
2015-09-05 Added lightcycle doxygen comments
2015-09-05 Added doxygen comments for Pong.cpp Fixed comment style
2015-09-05 Added doxygen comments for PixelShirtV2.cpp A little cleanup and spelling too
2015-09-12 Added comments for SuperSquare
2015-09-12 Added comments for the screen saver
2015-09-13 Added doxygen comments for tetris
2015-09-13 Added doxygen comments for Shooter
2015-09-13 Added GPLv3 headers
2015-09-13 astyle formatting
2015-09-13 Manual formatting
2015-09-13 Windows line endings
2015-09-13 Fixed naming, added doxyfile
2015-12-24 Pulled in latest NeoPixel library
2015-12-24 Folded platform specific code into this project It can compile for both Arduino and as a terminal application Broke out score display code into it's own file
2015-12-24 Added missing includes for Arduino build Renamed PixelShirtV2.cpp to PixelShirtV2.ino, for Arduino build Makefile still needs work Switched eclipse project type to makefile project
2015-12-24 Updated makefile to build .ino file
2015-12-24 Added PixelFighterGame Fixed keyboard analog input
2015-12-24 Ignore
2015-12-25 Fixed compilation for the older laptop
2015-12-25 Changed the way controller input is handled. Now it's done as the input arrives, rather than on the 32hz clock. This guarantees all input is processed. Updated documentation for PixelFighter Screensa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
2015-12-25 Fixed perma-jump if the button is held A little more documentation
2015-12-25 Cleanup and formatting
2015-12-26 Moved PixelFighter objects into the PixelFigterGame class
2015-12-27 Added checks for attacks & blocks between players
2016-01-06 Hitboxes are more accurate Pauses added during initialization and after hits Loser hidden after round is over
2016-01-06 Cleanup and notes
2016-01-09 Removed Jumping Added proper checks for overdraw (attacks and blocks always over body) Added logic to parry attacks during a window after the attack
2016-01-10 Added proper logic for blocking attacks, decrementing the correct HP Comments & formatting
2016-01-10 Fixed Pong for new input scheme
2016-01-10 Updated Shooter to work with new input scheme
2016-01-10 Added missing initializer
2016-01-10 Added better platform specific handling of input Commented out Super Square & Tetris for RAM space reasons Made managing games a little easier
2016-01-10 Reverted NeoPixel code. The new code was bigger and wouldn't fit Tetris
2016-01-10 Updated timer times for fighter
2016-01-10 Fixed input for Tetris for new input scheme Adjusted hit distance for PixelFighter Formatting
2016-02-15 Don't allow movement when attacking or blocking Removed references to jumping When an attack is blocked, the next one is now faster Finalized timers
2016-02-15 Fixed offset when looking for full lines to clear
2016-02-22 Fixed bug where cycle collisons were not detected
2016-02-24 Added images for README.md
2016-03-05 Added BOMs
2018-02-16 Added historical images
2018-02-16 Add history to README.md
2018-05-23 Backlink to CADLAB.io has been added.

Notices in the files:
Hardware/PixelShirtConsole/Eagle Files/PixelShirtConsole.brd:
Adam Feinstein (C) 2015
parts and their libraries:
SparkFun-Capacitors: Licensing: CC v3.0 Share-Alike You are welcome to use this library for commercial purposes.
SparkFun-Connectors: Licensing: Creative Commons ShareAlike 4.0 International - https://creativecommons.org/licenses/by-sa/4.0
